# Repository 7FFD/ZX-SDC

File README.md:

# ZX-SDC
Hardware version of z-controller (SD Card)

My motivation on creation this design was to avoid usage of CPLD and show that it's possible to design such controller with ICs.

This controller is intended to connect your ZX Spectrum / Clone with SD Card. That gives ability to copy files between SD Card with FAT16/32 to TRDOS (Beta Drive Interface), Nemo IDE and etc.

As an example, you can use FATALL file manager that runs from TRD.

## Technical information

This controller is almost fully compatible with original z-controller. There are couple of differences:
 - SD Card is always connected to power supply, besides it has power led connected to trigger to show state;
 - When /CS=1, means SD Card not selected, sending byte to data port is overwritten with 0xFF. It's a fix, because some SD Cards continue receiving input even after /CS becomes 1;

Control Port: 0x77
 - Bit 0: SD Card power On=1, Off=0;
 - Bit 1: SD Card /CS selected=0, deselected=1;
 - Rest bits are undefined;
   
Data Port: 0x57
 - Bit 0..7: Data byte to read/write; 

## Connection to ZX Spectrum Clones

Because current board design was done for ZXBUS, if you want to connect to your ZX Spectrum clone then you will need to solder adapter based on documentation for your computer.
Carefully check all signals, they are all important! As an example: /WAIT.

## Schematic preview

## Board preview

## Prototype

## Assembled and working board

## Note on assembling board

U11 and J4 has been added to the board for debugging purpose. Since board has been tested and doesn't need to be tuned if assembled correct, you can skip soldering U11 or use socket for it.
J4: 1-2 SD Card, 2-3 U11 Test IC connection

In case you decided to make sure that board assembled right and works correct, follow this checklist:
 1. Switch off computer
 2. Connect controller to ZXBUS Edge
 3. Remove SD Card if it was inserted at any slots
 4. Put jumper on J4 to 2-3
 5. Switch on computer - there are no leds should be ON
 6. Run commands from Basic:
    + "PRINT IN 87", expected result: 0
    + "PRINT IN 87", expected result: 255
    + "OUT 119,1", both leds must switch ON
    + "OUT 87,85"
    + "PRINT IN 87", expected result: 85
 7. Switch off computer
 8. Put jumper on J4 to 1-2
 9. Insert SD Card at any slot
 10. Switch on computer
 11. Run FATALL from ROM or from BDI
 12. SD Card should be detected and content will be shown on right panel

NOTE: SD Card must be formatted in FAT32/16!!!

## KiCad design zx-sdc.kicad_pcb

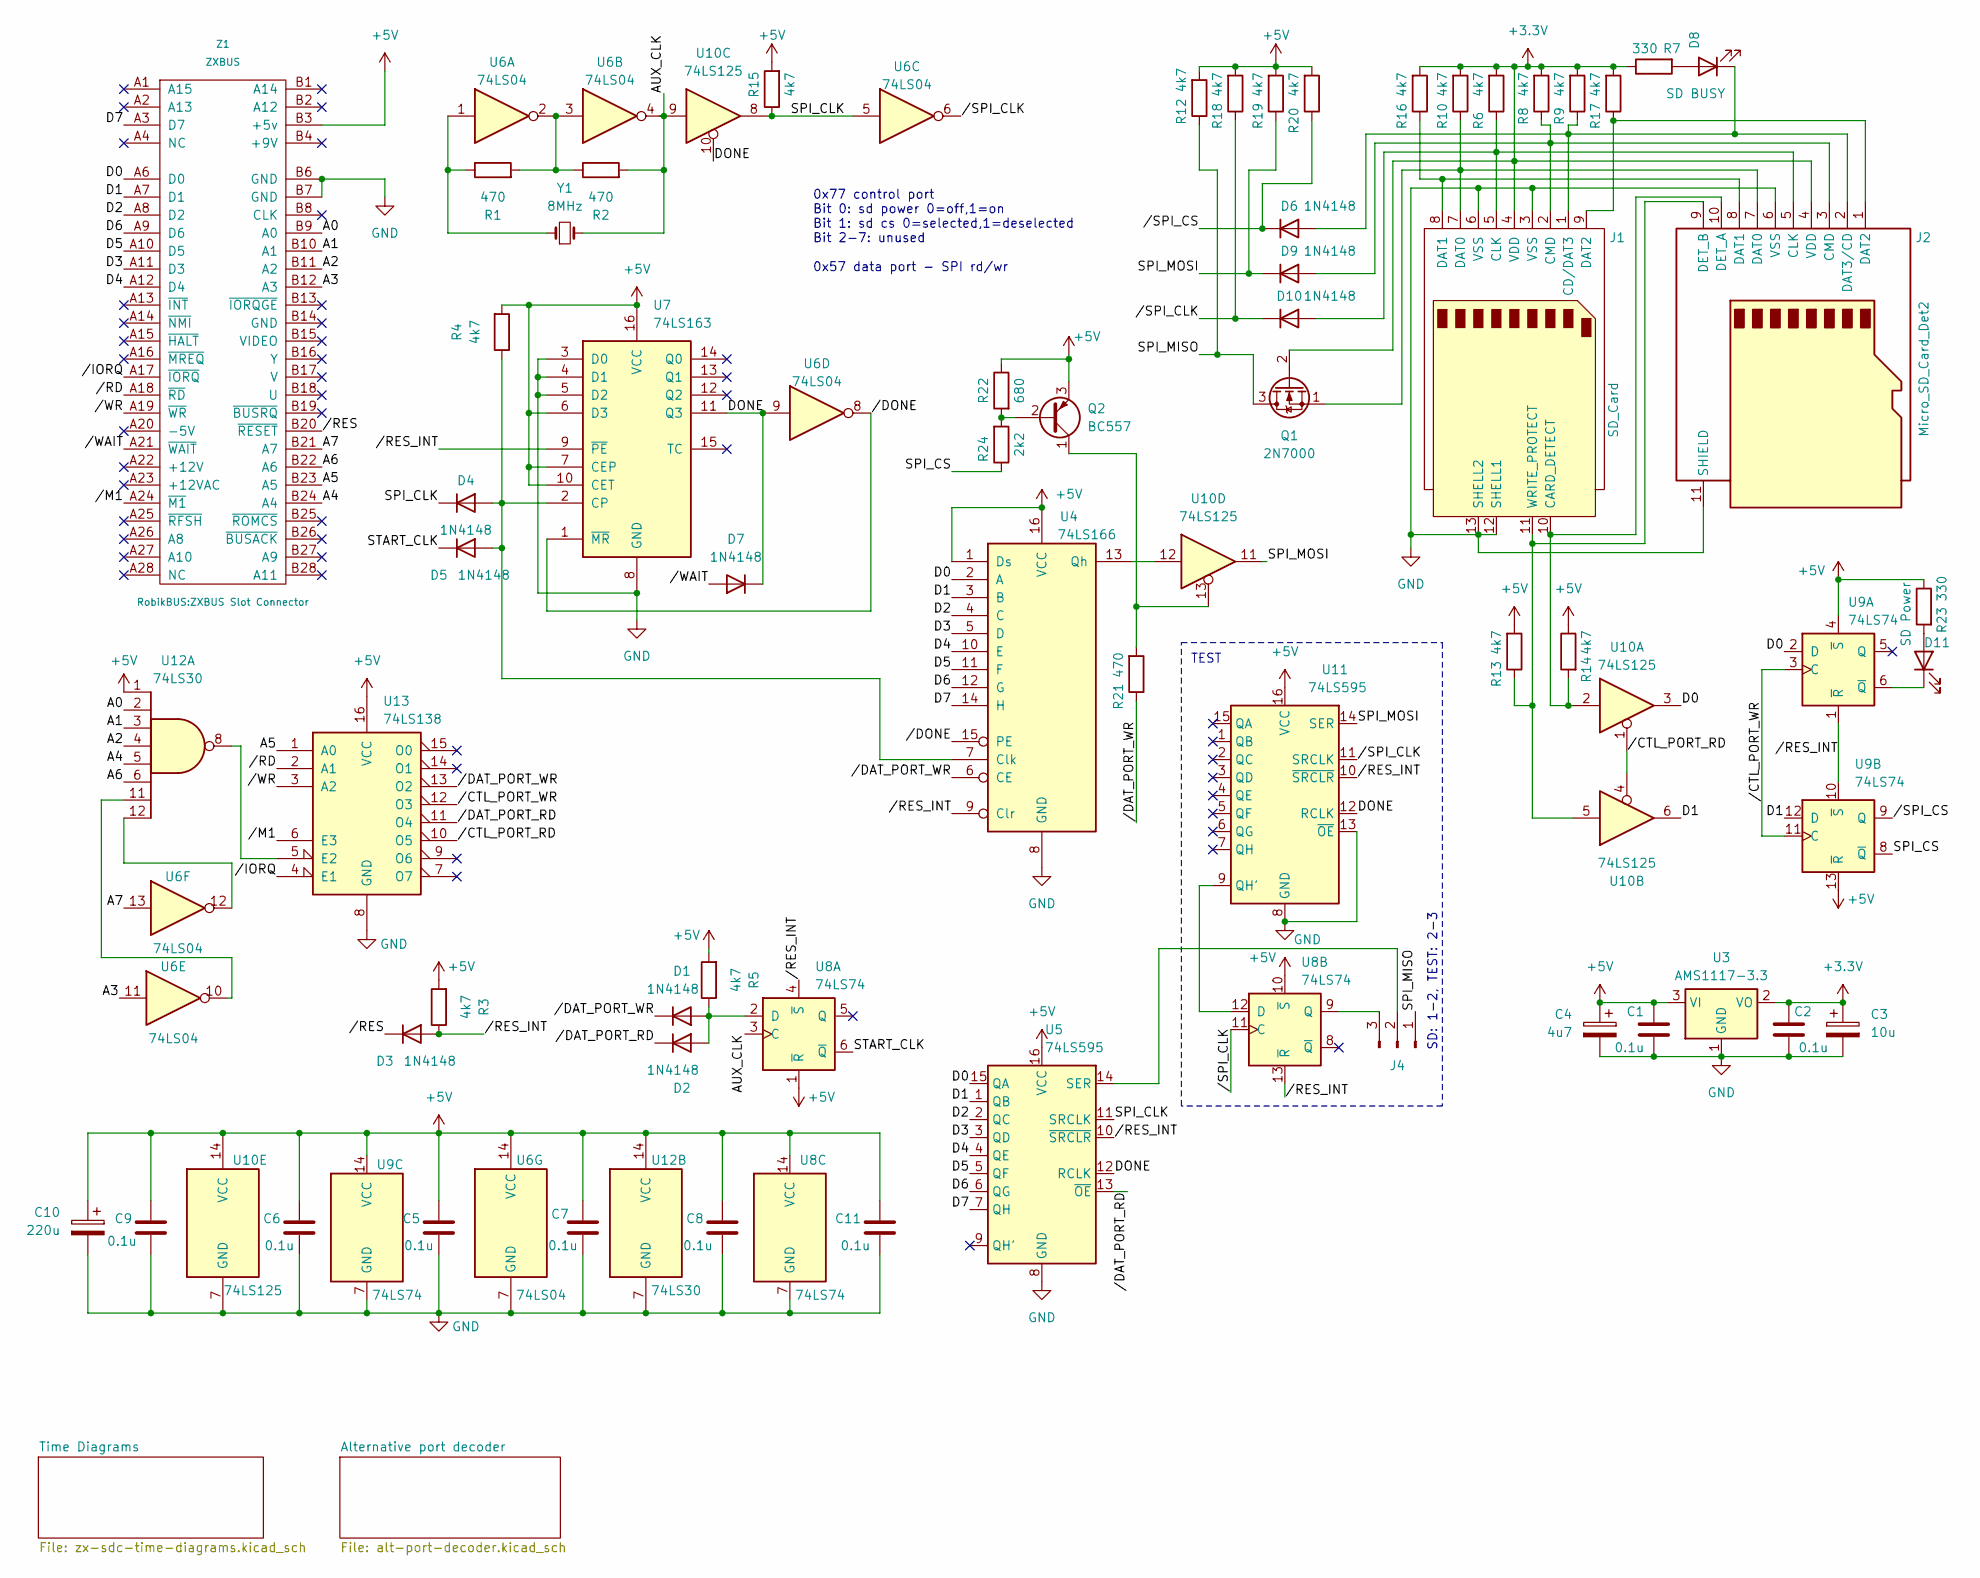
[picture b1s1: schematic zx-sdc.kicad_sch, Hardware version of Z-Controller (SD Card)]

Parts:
C1, C2, C5, C6, C7, C8, C9, C11: 0.1u; C_Disc_D4.7mm_W2.5mm_P5.00mm
C3: 10u; CP_Radial_D5.0mm_P2.00mm
C4: 4u7; CP_Radial_D5.0mm_P2.00mm
C10: 220u; CP_Radial_D5.0mm_P2.00mm
D1, D2, D3, D4, D5, D6, D7, D9, D10: 1N4148; D_DO-35_SOD27_P7.62mm_Horizontal
D8: SD BUSY; LED_D3.0mm
D11: SD Power; LED_D3.0mm
J1: SD_Card; SD_TE_2041021
J2: Micro_SD_Card_Det2; microSD_HC_Hirose_DM3AT-SF-PEJM5
J4: Conn_01x03_Pin; PinHeader_1x03_P2.54mm_Vertical
Q1: 2N7000; TO-92_Inline_Wide
Q2: BC557; TO-92_Inline_Wide
R1, R2, R21: 470; R_Axial_DIN0204_L3.6mm_D1.6mm_P5.08mm_Horizontal
R3, R4, R5, R6, R8, R9, R10, R12, R13, R14, R15, R16, R17, R18, R19, R20: 4k7; R_Axial_DIN0204_L3.6mm_D1.6mm_P5.08mm_Horizontal
R7, R23: 330; R_Axial_DIN0204_L3.6mm_D1.6mm_P5.08mm_Horizontal
R22: 680; R_Axial_DIN0204_L3.6mm_D1.6mm_P5.08mm_Horizontal
R24: 2k2; R_Axial_DIN0204_L3.6mm_D1.6mm_P5.08mm_Horizontal
U3: AMS1117-3.3; SOT-223-3_TabPin2
U4: 74LS166; DIP-16_W7.62mm
U5, U11: 74LS595; DIP-16_W7.62mm
U6: 74LS04; DIP-14_W7.62mm
U7: 74LS163; DIP-16_W7.62mm
U8, U9: 74LS74; DIP-14_W7.62mm
U10: 74LS125; DIP-14_W7.62mm
U12: 74LS30; DIP-14_W7.62mm
U13: 74LS138; DIP-16_W7.62mm
Y1: 8MHz; Crystal_HC18-U_Vertical
Z1: ZXBUS; ZXBUS Slot Connector

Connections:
+3.3V: C2.1, C3.1, J1.4 (VDD), J2.4 (VDD), Q1.2 (G), R6.2, R7.1, R8.2, R9.2, R10.2, R16.2, R17.2, U3.2 (VO)
+5V: C1.1, C4.1, C5.1, C6.1, C7.1, C8.1, C9.1, C10.1, C11.1, Q2.3 (E), R3.2, R4.2, R5.2, R12.2, R13.2, R14.1, R15.2, R18.2, R19.2, R20.2, R22.1, R23.1, U3.3 (VI), U4.1 (Ds), U4.16 (VCC), U5.16 (VCC), U6.14 (VCC), U7.6 (D3), U7.7 (CEP), U7.10 (CET), U7.16 (VCC), U8.1 (~R), U8.10 (~S), U8.14 (VCC), U9.4 (~S), U9.13 (~R), U9.14 (VCC), U10.14 (VCC), U11.16 (VCC), U12.1, U12.14 (VCC), U13.16 (VCC), Z1.B3 (+5v)
/A0: U12.2, Z1.B9 (A0)
/A1: U12.3, Z1.B10 (A1)
/A2: U12.4, Z1.B11 (A2)
/A3: U6.11, Z1.B12 (A3)
/A4: U12.5, Z1.B24 (A4)
/A5: U13.1 (A0), Z1.B23 (A5)
/A6: U12.6, Z1.B22 (A6)
/A7: U6.13, Z1.B21 (A7)
/AUX_CLK: R2.2, U6.4, U8.3 (C), U10.9, Y1.2
/D0: U4.2 (A), U5.15 (QA), U9.2 (D), U10.3, Z1.A6 (D0)
/D1: U4.3 (B), U5.1 (QB), U9.12 (D), U10.6, Z1.A7 (D1)
/D2: U4.4 (C), U5.2 (QC), Z1.A8 (D2)
/D3: U4.5 (D), U5.3 (QD), Z1.A11 (D3)
/D4: U4.10 (E), U5.4 (QE), Z1.A12 (D4)
/D5: U4.11 (F), U5.5 (QF), Z1.A10 (D5)
/D6: U4.12 (G), U5.6 (QG), Z1.A9 (D6)
/D7: U4.14 (H), U5.7 (QH), Z1.A3 (D7)
/DONE: D7.1 (K), U5.12 (RCLK), U6.9, U7.11 (Q3), U10.10, U11.12 (RCLK)
/SPI_CLK: D4.1 (K), R15.1, U5.11 (SRCLK), U6.5, U10.8
/SPI_CS: R24.1, U9.8 (~Q)
/SPI_MISO: J4.1, Q1.3 (D), R12.1
/SPI_MOSI: D9.1 (K), R19.1, U10.11, U11.14 (SER)
/START_CLK: D5.1 (K), U8.6 (~Q)
//CTL_PORT_RD: U10.1, U10.4, U13.10 (O5)
//CTL_PORT_WR: U9.3 (C), U9.11 (C), U13.12 (O3)
//DAT_PORT_RD: D2.1 (K), U5.13 (~OE), U13.11 (O4)
//DAT_PORT_WR: D1.1 (K), R21.1, U4.6 (CE), U13.13 (O2)
//DONE: U4.15 (PE), U6.8, U7.1 (~MR)
//IORQ: U13.4 (E1), Z1.A17 (~IORQ)
//M1: U13.6 (E3), Z1.A24 (~M1)
//RD: U13.2 (A1), Z1.A18 (~RD)
//RES: D3.1 (K), Z1.B20 (~RESET)
//RES_INT: D3.2 (A), R3.1, U4.9 (Clr), U5.10 (~SRCLR), U7.9 (~PE), U8.4 (~S), U8.13 (~R), U9.1 (~R), U9.10 (~S), U11.10 (~SRCLR)
//SPI_CLK: D10.1 (K), R18.1, U6.6, U8.11 (C), U11.11 (SRCLK)
//SPI_CS: D6.1 (K), R20.1, U9.9 (Q)
//WAIT: D7.2 (A), Z1.A21 (~WAIT)
//WR: U13.3 (A2), Z1.A19 (~WR)
GND: C1.2, C2.2, C3.2, C4.2, C5.2, C6.2, C7.2, C8.2, C9.2, C10.2, C11.2, J1.3 (VSS), J1.6 (VSS), J1.12 (SHELL1), J1.13 (SHELL2), J2.6 (VSS), J2.11 (SHIELD), U3.1 (GND), U4.8 (GND), U5.8 (GND), U6.7 (GND), U7.3 (D0), U7.4 (D1), U7.5 (D2), U7.8 (GND), U8.7 (GND), U9.7 (GND), U10.7 (GND), U11.8 (GND), U11.13 (~OE), U12.7 (GND), U13.8 (GND), Z1.B6 (GND), Z1.B7 (GND)
unnamed: D1.2 (A), D2.2 (A), R5.1, U8.2 (D)
unnamed: D4.2 (A), D5.2 (A), R4.1, U4.7 (Clk), U7.2 (CP)
unnamed: D6.2 (A), D8.1 (K), J1.1 (CD/DAT3), J2.2 (DAT3/CD), R9.1
unnamed: D8.2 (A), R7.2
unnamed: D9.2 (A), J1.2 (CMD), J2.3 (CMD), R8.1
unnamed: D10.2 (A), J1.5 (CLK), J2.5 (CLK), R6.1
unnamed: D11.2 (A), R23.2
unnamed: D11.1 (K), U9.6 (~Q)
unnamed: J1.10 (CARD_DETECT), J2.10 (DET_A), R14.2, U10.2
unnamed: J1.7 (DAT0), J2.7 (DAT0), Q1.1 (S), R10.1
unnamed: J1.8 (DAT1), J2.8 (DAT1), R16.1
unnamed: J1.9 (DAT2), J2.1 (DAT2), R17.1
unnamed: J1.11 (WRITE_PROTECT), J2.9 (DET_B), R13.1, U10.5
unnamed: J4.2, U5.14 (SER)
unnamed: J4.3, U8.9 (Q)
unnamed: Q2.2 (B), R22.2, R24.2
unnamed: Q2.1 (C), R21.2, U10.13
unnamed: R1.1, U6.1, Y1.1
unnamed: R1.2, R2.1, U6.2, U6.3
unnamed: U4.13 (Qh), U10.12
unnamed: U8.12 (D), U11.9 (QH')
unnamed: U6.10, U12.11
unnamed: U6.12, U12.12
unnamed: U12.8, U13.5 (E2)

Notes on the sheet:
SD: 1-2, TEST: 2-3
TEST
0x77 control port Bit 0: sd power 0=off,1=on Bit 1: sd cs 0=selected,1=deselected Bit 2-7: unused 0x57 data port - SPI rd/wr

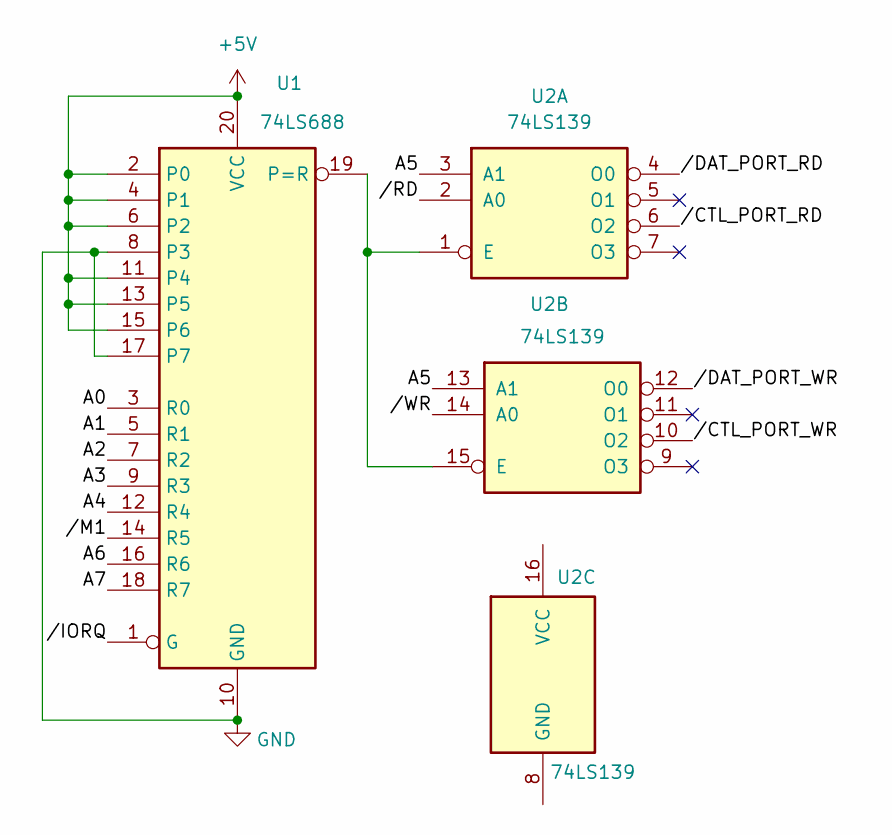
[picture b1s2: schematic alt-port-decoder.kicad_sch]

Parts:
U1: 74LS688
U2: 74LS139

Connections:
unnamed: U1.8 (P3), U1.10 (GND), U1.17 (P7)
unnamed: U1.2 (P0), U1.4 (P1), U1.6 (P2), U1.11 (P4), U1.13 (P5), U1.15 (P6), U1.20 (VCC)
unnamed: U1.19 (P=R), U2.1 (E), U2.15 (E)
unnamed: U2.3 (A1), U2.13 (A1)

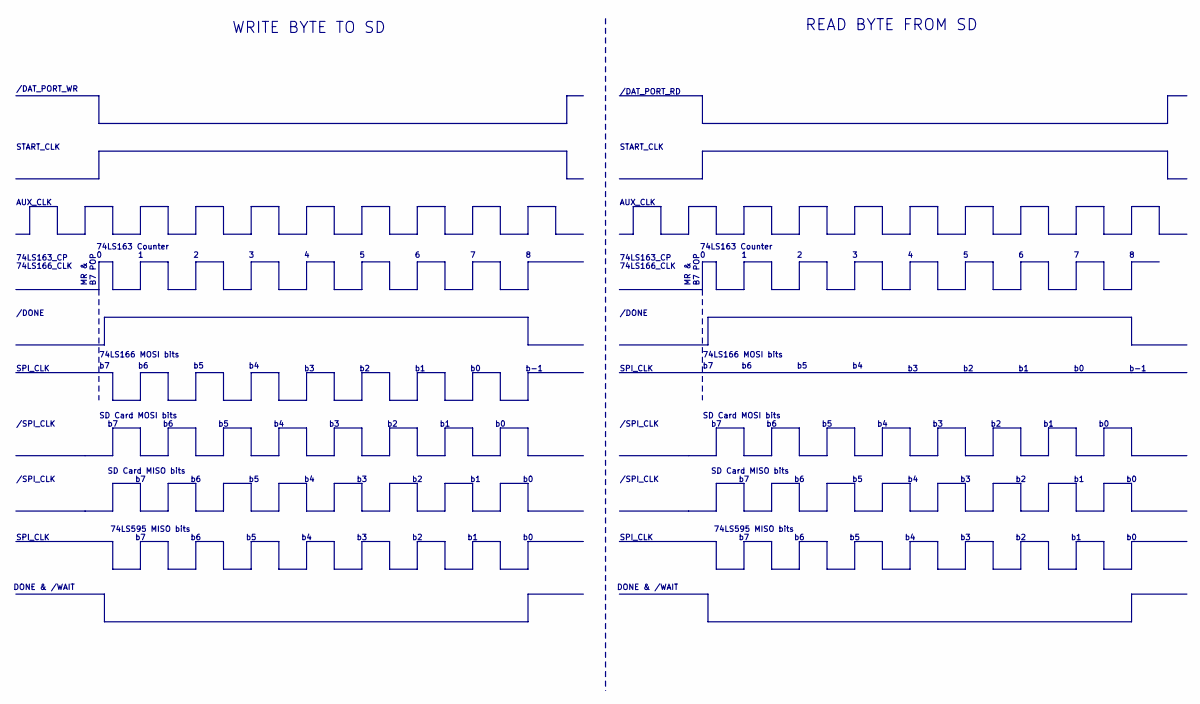
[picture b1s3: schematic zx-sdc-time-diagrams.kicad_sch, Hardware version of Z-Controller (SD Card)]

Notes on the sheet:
/DONE
74LS166 MOSI bits
b-1
READ BYTE FROM SD
DONE & /WAIT
SPI_CLK
WRITE BYTE TO SD
74LS166_CLK
74LS595 MISO bits
/SPI_CLK
START_CLK
AUX_CLK
SD Card MOSI bits
74LS163 Counter
/DAT_PORT_WR
SD Card MISO bits
/DAT_PORT_RD
74LS163_CP
MR & B7 POP

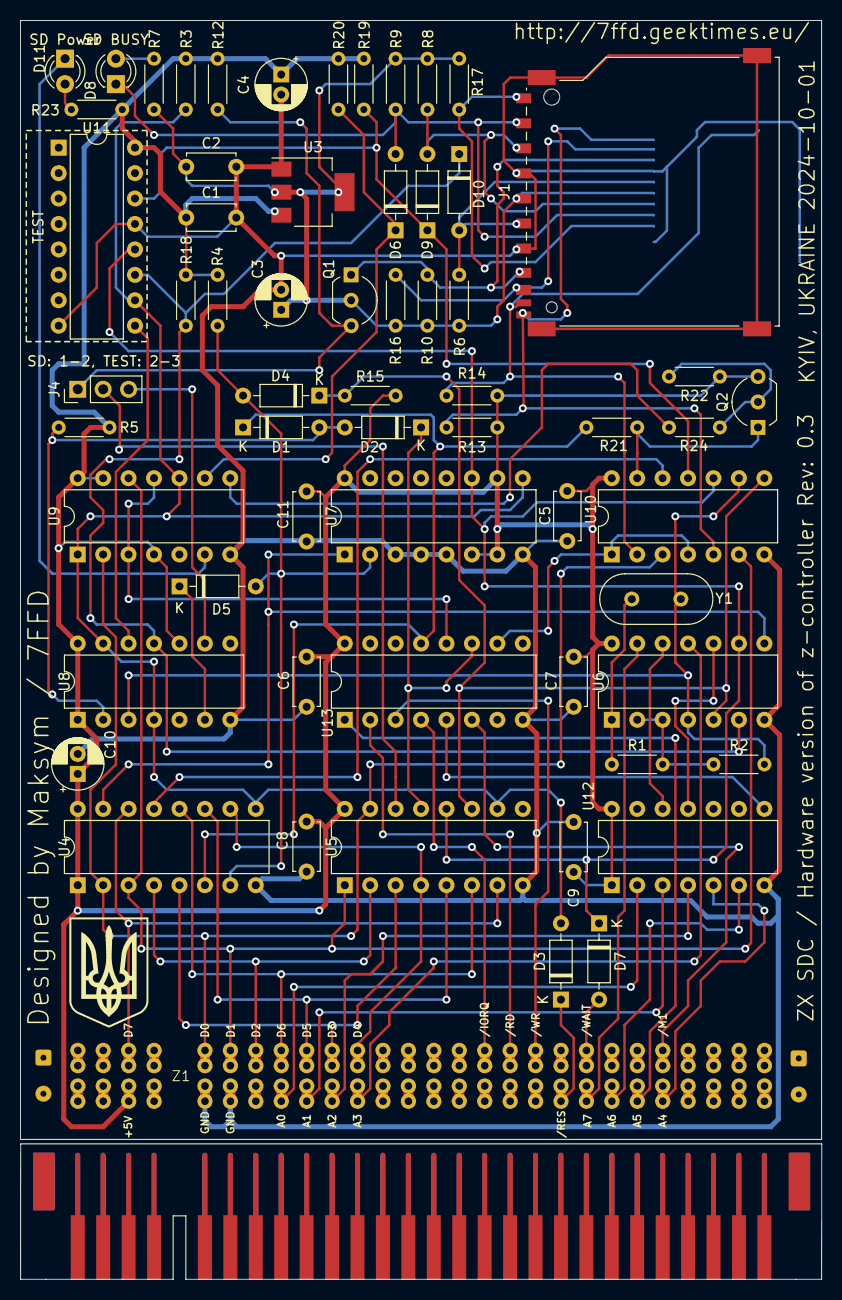
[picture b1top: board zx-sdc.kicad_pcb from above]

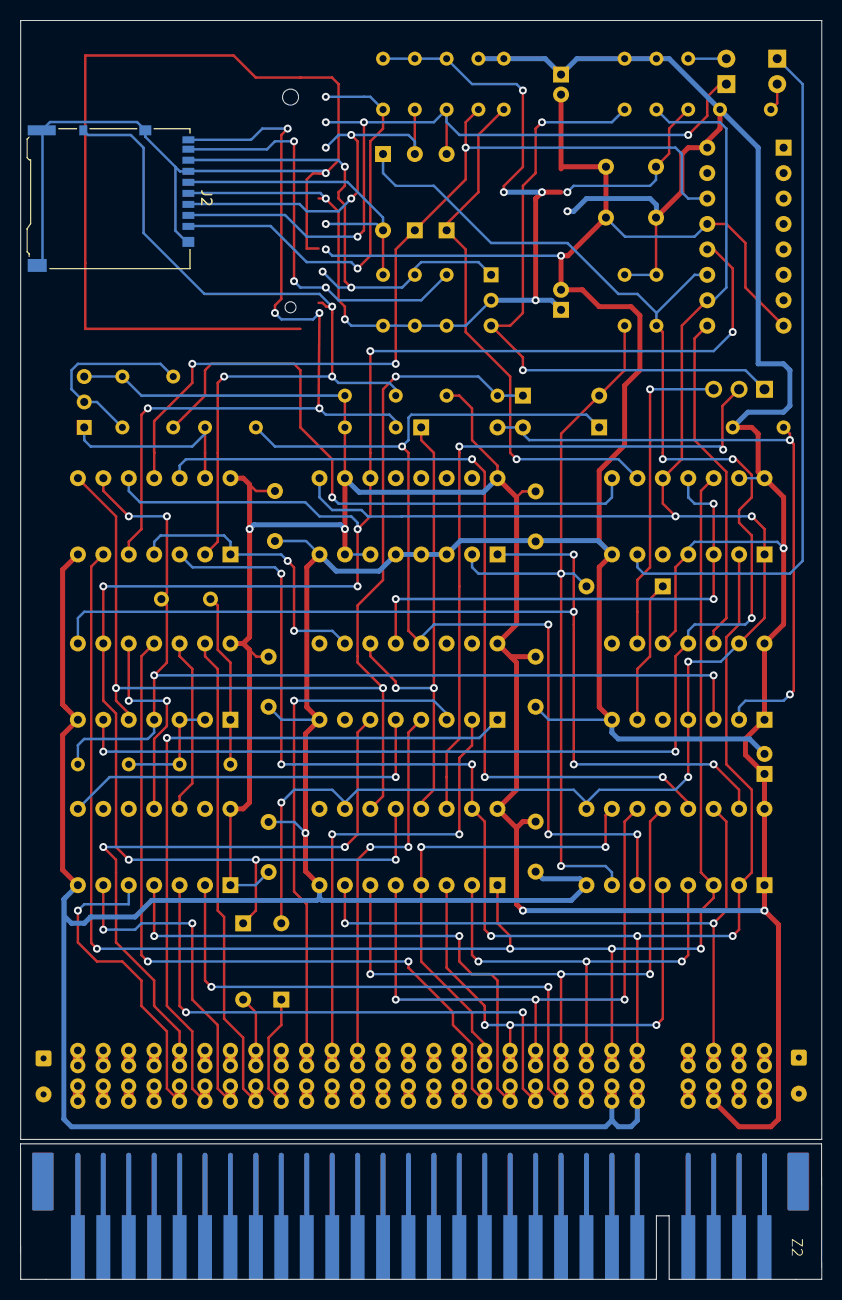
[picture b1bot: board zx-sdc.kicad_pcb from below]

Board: 2 copper layers, 80.0 x 125.7 mm, 65 parts (2 on the bottom side), 64 nets.

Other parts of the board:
UA CoA: UA CoA 8x11mm
Z2: ZXBUS

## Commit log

2024-10-03 - added time diagram - created backup v0.1 - created backup v0.2 - added various changes
2024-10-03 Started ZX-SDC project, hardware version of Z-Controller
2024-10-03 completed design of ZX SDC
2024-10-03 preparation for board design
2024-10-03 refinings & last cuts
2024-10-03 fixed revision number
2024-10-03 fixed and annotated SD/TEST jumpers
2024-10-03 Added schematic and 3d view for readme
2024-10-03 Replaced schematic file with fixes
2024-10-03 added photos of working prototype
2024-10-27 Added assembled board and run tests
2025-02-10 moved microsd slot close to edge
